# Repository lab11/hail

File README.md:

Hail
====

Hail is an IoT development module that runs the
[Tock](https://github.com/helena-project/tock) operating system.
Its features:

- [SAM4L](http://www.atmel.com/products/microcontrollers/arm/sam4l.aspx) Cortex-M4
- [nRF51822](https://www.nordicsemi.com/eng/Products/Bluetooth-low-energy/nRF51822) BLE Radio
- [SI7021](https://www.silabs.com/products/sensors/humidity-sensors/Pages/si7013-20-21.aspx) Temperature and Humidity Sensor
- [ISL29035](https://www.intersil.com/en/products/optoelectronics/ambient-light-sensors/light-to-digital-sensors/ISL29035.html) Light Sensor
- [FXOS8700CQ](http://www.nxp.com/products/sensors/6-axis-sensors/digital-sensor-3d-accelerometer-2g-4g-8g-plus-3d-magnetometer:FXOS8700CQ) 6-axis Accelerometer and Magnetometer
- RGB LED
- USB Programming
- Particle [Photon](https://www.particle.io/products/hardware/photon-wifi-dev-kit) Form-Factor and Pinout

**[Buy Now!](https://www.tockos.org/hardware/)**

Hail + Tock
-----------

[TockOS](https://github.com/helena-project/tock/tree/master/boards/hail)
supports Hail. See the instructions there for how to program the Tock kernel
and applications.

Bootloader
----------

Hail supports a software bootloader which allows new code to be flashed
over USB. The bootloader source is in the [bootloader](bootloader) directory.
The [tockloader](https://github.com/helena-project/tockloader) utility
can flash applications using the bootloader.

Commissioning New Hail Boards
-----------------------------

There a couple steps to provision a newly populated Hail board.
See the [commissioning](commissioning) folder for more information.

nRF51822 BLE Radio
------------------

By default, the nRF51822 is commissioned with the
[serialization](https://github.com/helena-project/tock-nrf-serialization)
application which allows softdevice commands to be sent over a UART connection
from the SAM4L.

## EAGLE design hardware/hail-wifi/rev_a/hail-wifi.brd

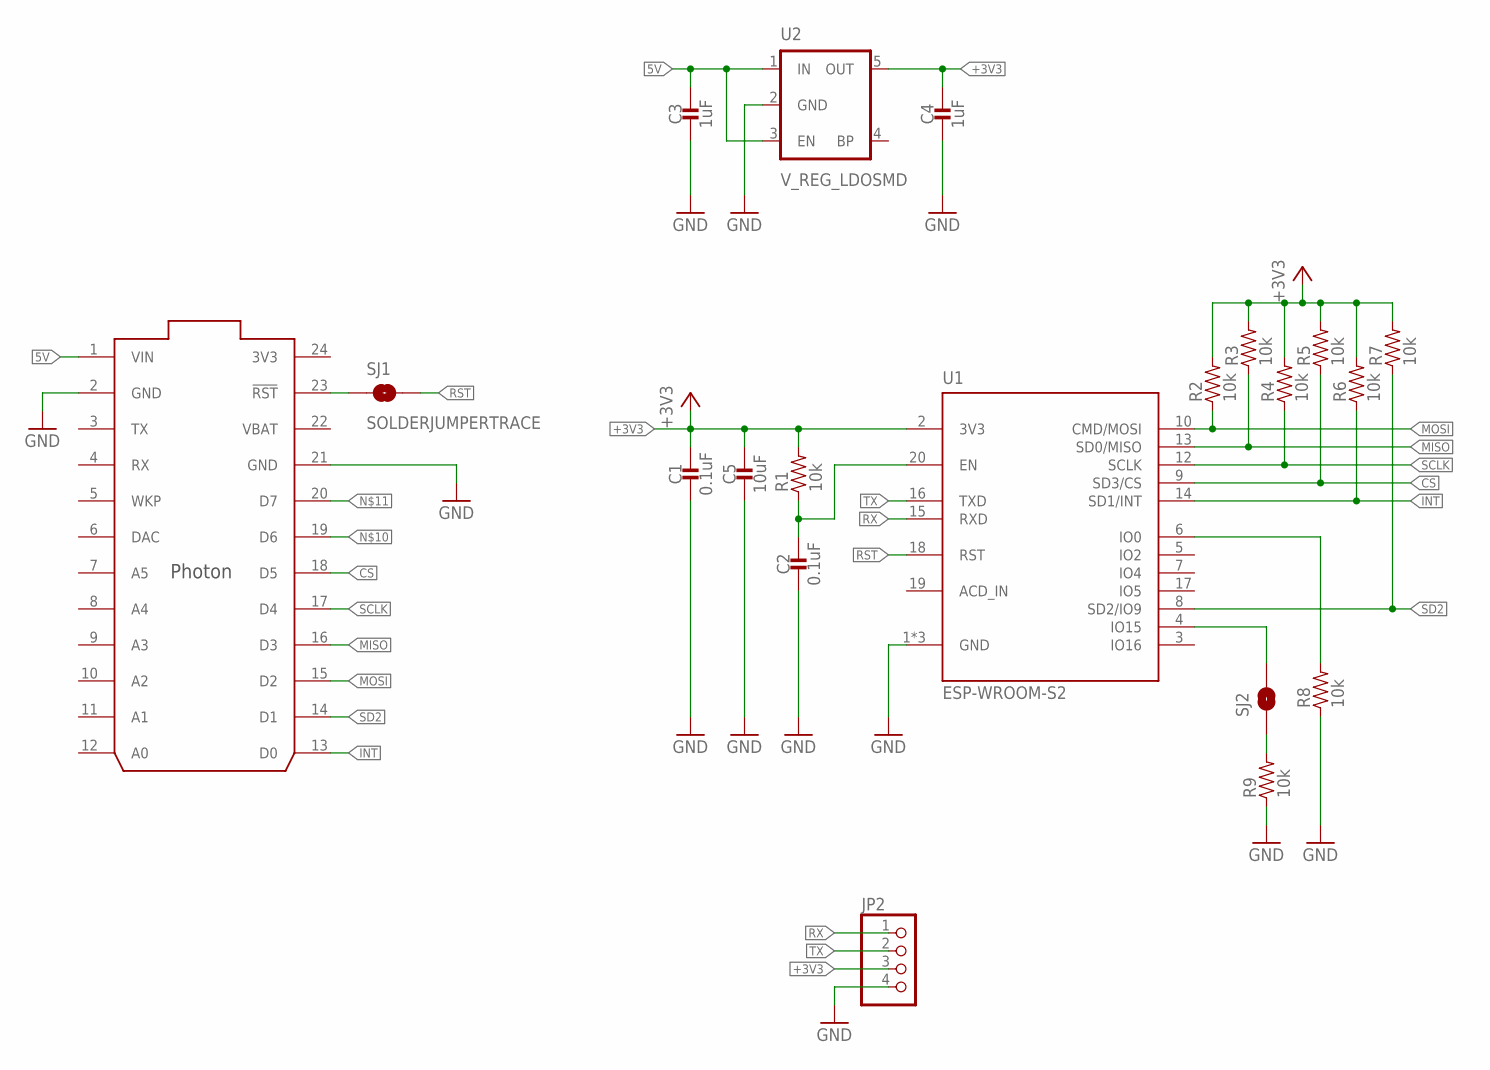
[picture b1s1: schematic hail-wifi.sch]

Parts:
C1, C2: 0.1uF; 0603_CAP
C3, C4: 1uF; 0603_CAP
C5: 10uF; 0603_CAP
JP2: PINHD-1X4/90; 1X04/90
R1, R2, R3, R4, R5, R6, R7, R8, R9: 10k; 0603-RES
SJ1: SOLDERJUMPERTRACE; SJ_2S-TRACE
SJ2: SOLDERJUMPERNO; SJ_2S-NO
U1: ESP-WROOM-S2
U2: V_REG_LDOSMD; SOT23-5
U3: PHOTON_WITH_HEADERS; PHOTON

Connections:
3V3: U3.24 (3V3)
5V: C3.1, U2.1 (IN), U2.3 (EN), U3.1 (VIN)
+3V3: C1.1, C4.1, C5.1, JP2.3, R1.2, R2.2, R3.2, R4.2, R5.2, R6.2, R7.2, U1.2 (3V3), U2.5 (OUT)
CS: R5.1, U1.9 (SD3/CS), U3.18 (D5)
GND: C1.2, C2.2, C3.2, C4.2, C5.2, JP2.4, R8.1, R9.1, U1.1 (GND), U1.11 (GND), U1.21 (GND), U2.2 (GND), U3.2 (GND), U3.21 (GND)
INT: R6.1, U1.14 (SD1/INT), U3.13 (D0)
MISO: R3.1, U1.13 (SD0/MISO), U3.16 (D3)
MOSI: R2.1, U1.10 (CMD/MOSI), U3.15 (D2)
unnamed: SJ2.2, U1.4 (IO15)
unnamed: SJ1.1, U3.23 (!RST)
unnamed: R9.2, SJ2.1
unnamed: R8.2, U1.6 (IO0)
unnamed: C2.1, R1.1, U1.20 (EN)
RST: SJ1.2, U1.18 (RST)
RX: JP2.1, U1.15 (RXD)
SCLK: R4.1, U1.12 (SCLK), U3.17 (D4)
SD2: R7.1, U1.8 (SD2/IO9), U3.14 (D1)
TX: JP2.2, U1.16 (TXD)
VBAT: U3.22 (VBAT)

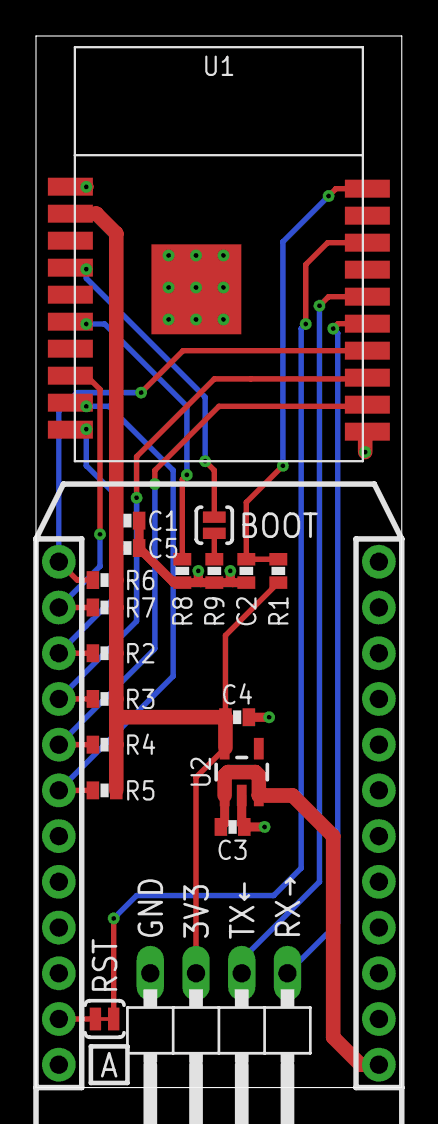
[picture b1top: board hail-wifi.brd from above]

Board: 2 copper layers, 20.3 x 58.4 mm, 20 parts (0 on the bottom side), 17 nets.

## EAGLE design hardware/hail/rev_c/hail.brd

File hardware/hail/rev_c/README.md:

Hardware files
==============

Hail was created in [Eagle](http://www.autodesk.com/products/eagle/overview) and the `hail.sch` and
`hail.brd` files are Eagle schematic and board files respectively.

`hail_bom.xlsx` is the Bill of Materials (list of parts). It is also provided
as `.txt` and `.csv` files for convenience.

Rev C changes
-------------

 * Connected ADVREFP to VDDANA.
 * Replace Lab11 logo with text. In practice, it didn't print correctly.

License
-------

<br />
This work is licensed under a
<a rel="license" href="http://creativecommons.org/licenses/by-sa/4.0/">Creative Commons Attribution-ShareAlike 4.0 International License</a>.

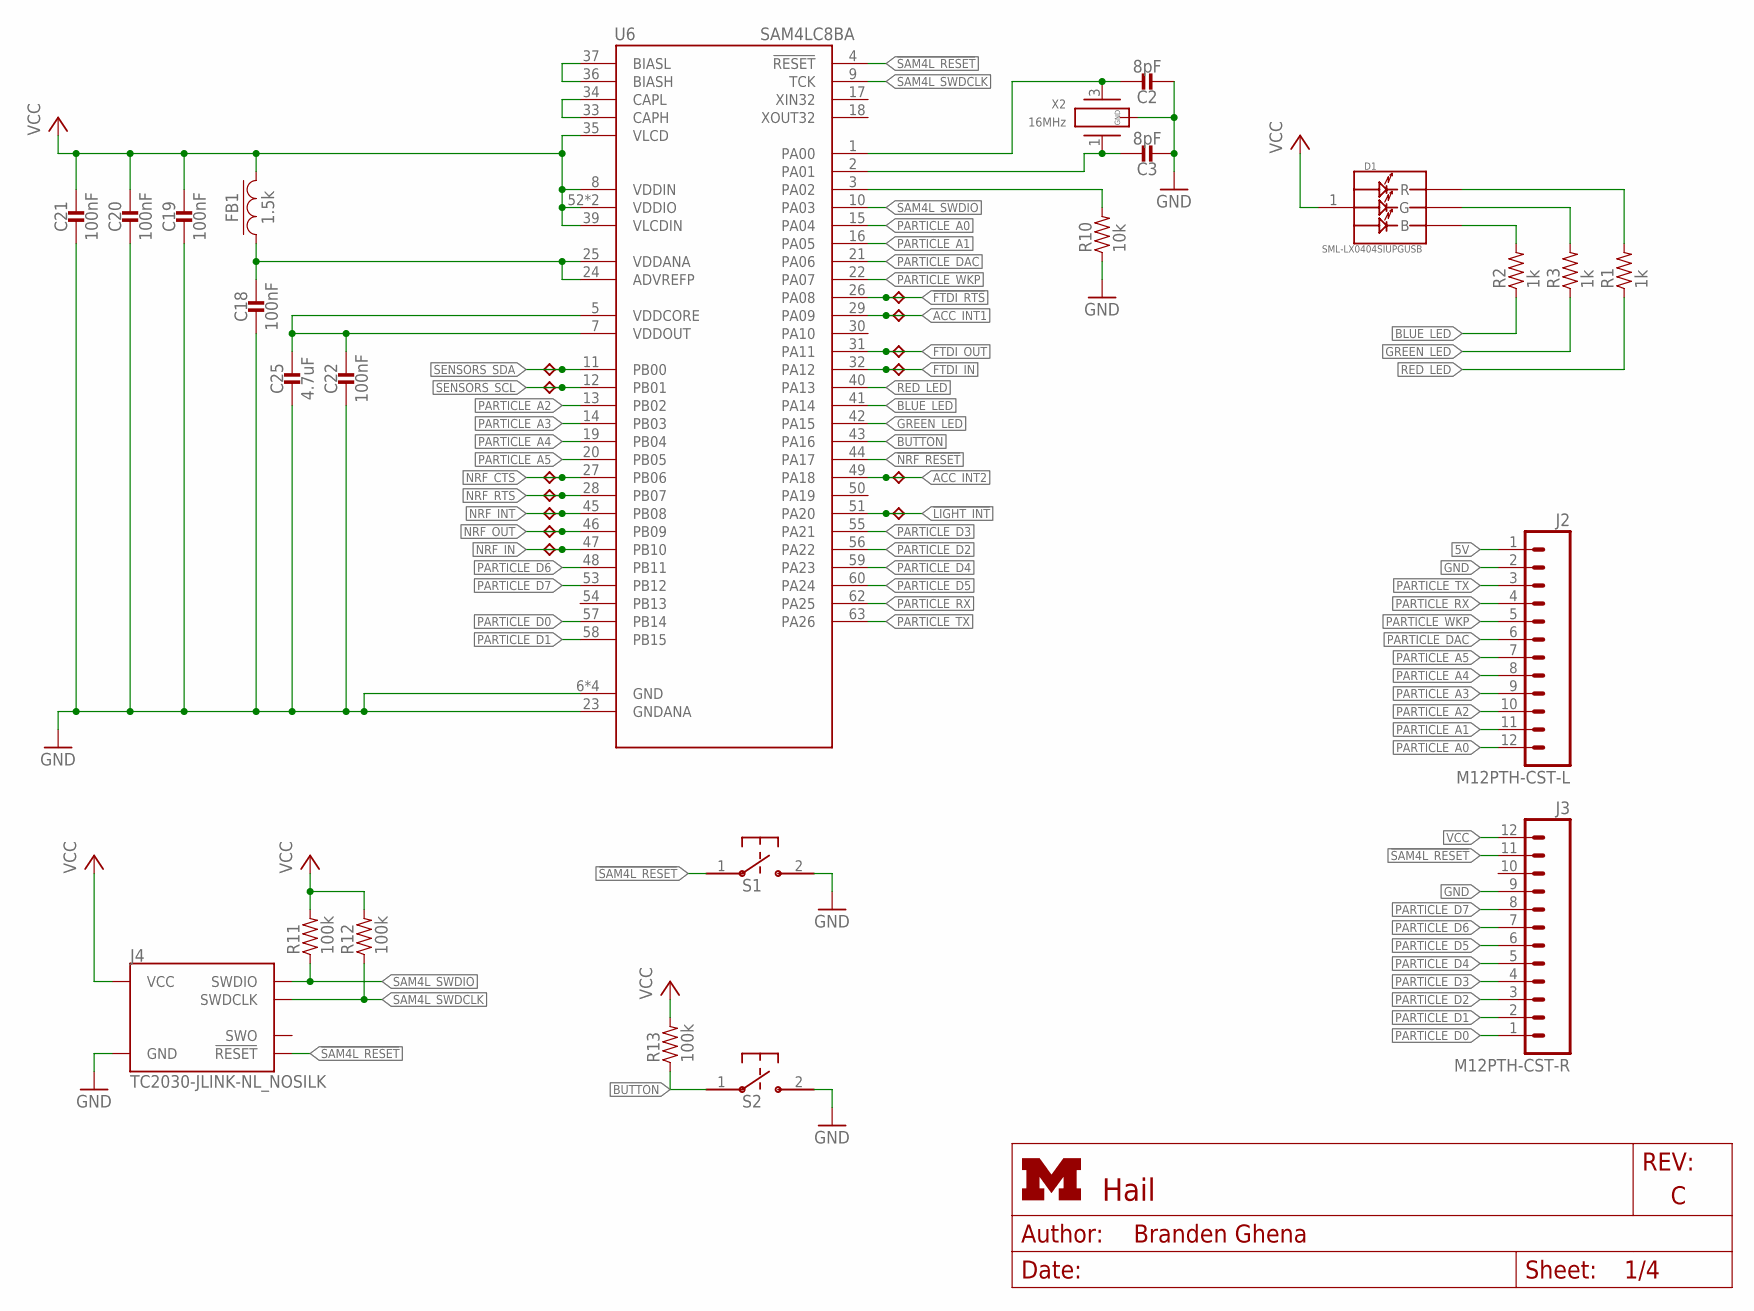
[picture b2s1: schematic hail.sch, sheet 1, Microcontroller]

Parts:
C2, C3: 8pF; 0402_CAP; MPN GRM1555C1H8R0BA01D; DIGIKEY 490-8230-1-ND
C18, C19, C20, C21, C22: 100nF; 0402_CAP; MPN MF-CAP-0402-0.1uF; DIGIKEY 490-10777-1-ND
C25: 4.7uF; 0402_CAP; MPN ZRB15XR61A475KE01D; DIGIKEY 490-13252-1-ND
D1: SML-LX0404SIUPGUSB; 1MM_SQ_4PAD; MPN SML-LX0404SIUPGUSB
FB1: 1.5k; 0402_CAP; MPN CIM05J152NC; DIGIKEY 1276-6395-1-ND
J2: M12PTH-CST-L; 1X12-CASTELLATED; MPN MF-CON-2.54mm-01x12; DIGIKEY S1011E-12-ND
J3: M12PTH-CST-R; 1X12-CASTELLATED; MPN MF-CON-2.54mm-01x12; DIGIKEY S1011E-12-ND
J4: TC2030-JLINK-NL_NOSILK; TC2030-IDC-NL_NOSILK
R1, R2, R3: 1k; 0402_RES; MPN MF-RES-0402-1K; DIGIKEY 1276-3430-1-ND
R10: 10k; 0402_RES; MPN MF-RES-0402-10K; DIGIKEY 1276-3431-1-ND
R11, R12, R13: 100k; 0402_RES; MPN MF-RES-0402-100K; DIGIKEY 1276-3432-1-ND
S1, S2: B3U-1000P; MPN B3U-1000P
TP1, TP2, TP3, TP4, TP5, TP6, TP7, TP8, TP9, TP10, TP11, TP12, TP13: TPB1,27; B1,27
U6: SAM4LC8BA; QFN-64-9MM; MPN ATSAM4LC8BA-MU; DIGIKEY ATSAM4LC8BA-MURCT-ND
X2: 16MHz; FHXXX; MPN FH1600015

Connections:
5V: J2.1 (12); also elsewhere on the board
!FTDI_RTS: TP11.TP, U6.26 (PA08); also elsewhere on the board
!LIGHT_INT: TP10.TP, U6.51 (PA20); also elsewhere on the board
!NRF_RESET: U6.44 (PA17); also elsewhere on the board
!SAM4L_RESET: J3.11, J4.3 (!RESET), S1.1, U6.4 (!RESET); also elsewhere on the board
ACC_INT1: TP8.TP, U6.29 (PA09); also elsewhere on the board
ACC_INT2: TP9.TP, U6.49 (PA18); also elsewhere on the board
BLUE_LED: R2.1, U6.41 (PA14)
BUCK/LDO_N1: R10.2, U6.3 (PA02)
BUTTON: R13.1, S2.1, U6.43 (PA16)
FTDI_IN: TP13.TP, U6.32 (PA12); also elsewhere on the board
FTDI_OUT: TP12.TP, U6.31 (PA11); also elsewhere on the board
GND: C2.2, C3.2, C18.2, C19.2, C20.2, C21.2, C22.2, C25.2, J2.2 (11), J3.9, J4.5 (GND), R10.1, S1.2, S2.2, U6.6 (GND), U6.23 (GNDANA), U6.38 (GND), U6.64 (GND), U6.GND, X2.2 (GND), X2.4 (GND); also elsewhere on the board
GREEN_LED: R3.1, U6.42 (PA15)
unnamed: D1.3 (B), R2.2
unnamed: D1.4 (G), R3.2
unnamed: D1.2 (R), R1.2
unnamed: U6.36 (BIASH), U6.37 (BIASL)
unnamed: U6.33 (CAPH), U6.34 (CAPL)
unnamed: C18.1, FB1.1, U6.24 (ADVREFP), U6.25 (VDDANA)
unnamed: C22.1, C25.1, U6.5 (VDDCORE), U6.7 (VDDOUT)
NRF_CTS: TP1.TP, U6.27 (PB06); also elsewhere on the board
NRF_IN: TP5.TP, U6.47 (PB10); also elsewhere on the board
NRF_INT: TP3.TP, U6.45 (PB08); also elsewhere on the board
NRF_OUT: TP4.TP, U6.46 (PB09); also elsewhere on the board
NRF_RTS: TP2.TP, U6.28 (PB07); also elsewhere on the board
PARTICLE_A0: J2.12 (1), U6.15 (PA04)
PARTICLE_A1: J2.11 (2), U6.16 (PA05)
PARTICLE_A2: J2.10 (3), U6.13 (PB02)
PARTICLE_A3: J2.9 (4), U6.14 (PB03)
PARTICLE_A4: J2.8 (5), U6.19 (PB04)
PARTICLE_A5: J2.7 (6), U6.20 (PB05)
PARTICLE_D0: J3.1, U6.57 (PB14)
PARTICLE_D1: J3.2, U6.58 (PB15)
PARTICLE_D2: J3.3, U6.56 (PA22)
PARTICLE_D3: J3.4, U6.55 (PA21)
PARTICLE_D4: J3.5, U6.59 (PA23)
PARTICLE_D5: J3.6, U6.60 (PA24)
PARTICLE_D6: J3.7, U6.48 (PB11)
PARTICLE_D7: J3.8, U6.53 (PB12)
PARTICLE_DAC: J2.6 (7), U6.21 (PA06)
PARTICLE_RX: J2.4 (9), U6.62 (PA25)
PARTICLE_TX: J2.3 (10), U6.63 (PA26)
PARTICLE_WKP: J2.5 (8), U6.22 (PA07)
RED_LED: R1.1, U6.40 (PA13)
SAM4L_SWDCLK: J4.4 (SWDCLK), R12.1, U6.9 (TCK)
SAM4L_SWDIO: J4.2 (SWDIO), R11.1, U6.10 (PA03)
SAM4L_XIN1: C2.1, U6.1 (PA00), X2.3 (2)
SAM4L_XOUT1: C3.1, U6.2 (PA01), X2.1
SENSORS_SCL: TP7.TP, U6.12 (PB01); also elsewhere on the board
SENSORS_SDA: TP6.TP, U6.11 (PB00); also elsewhere on the board
VCC: C19.1, C20.1, C21.1, D1.1 (VDD), FB1.2, J3.12, J4.1 (VCC), R11.2, R12.2, R13.2, U6.8 (VDDIN), U6.35 (VLCD), U6.39 (VLCDIN), U6.52 (VDDIO), U6.61 (VDDIO); also elsewhere on the board

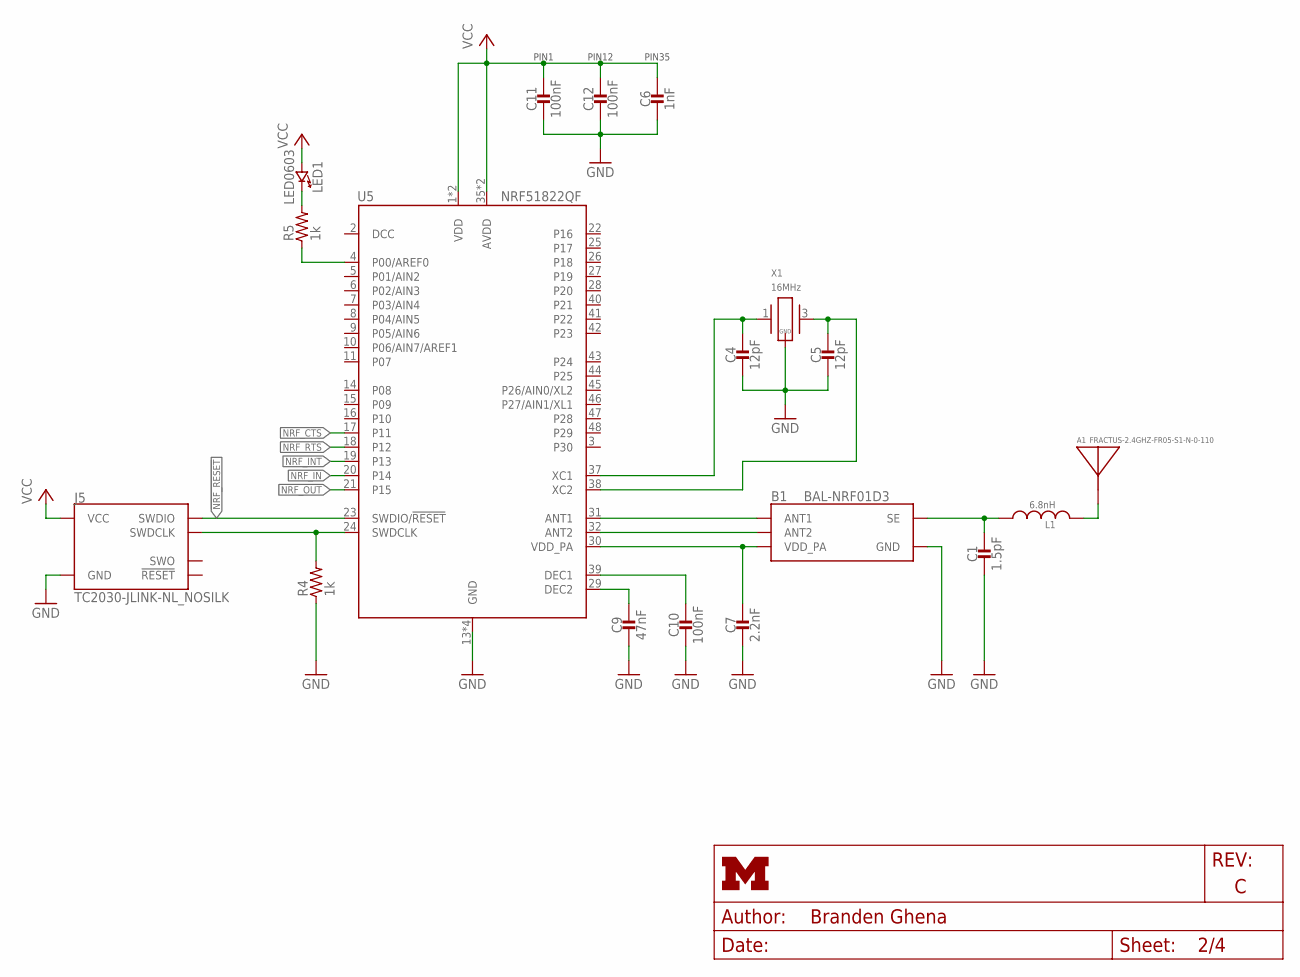
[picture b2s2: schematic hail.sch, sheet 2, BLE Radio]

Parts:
A1: FRACTUS-2.4GHZ-FR05-S1-N-0-110; FRACTUS-ANTENNA-FR05-S1-N-0-110; MPN FR05-S1-N-0110B
B1: BAL-NRF01D3; MPN BAL-NRF01D3
C1: 1.5pF; 0402_CAP; MPN GRM1555C1H1R5BA01D; DIGIKEY 490-6212-1-ND
C4, C5: 12pF; 0402_CAP; MPN GRM1555C1H120GA01D; DIGIKEY 490-6197-1-ND
C6: 1nF; 0402_CAP; MPN MF-CAP-0402-1nF; DIGIKEY 490-1303-1-ND
C7: 2.2nF; 0402_CAP; MPN GRM155R71E222KA01D; DIGIKEY 490-5419-1-ND
C9: 47nF; 0402_CAP; MPN C1005X7R1C473K050BC; DIGIKEY 445-1264-1-ND
C10, C11, C12: 100nF; 0402_CAP; MPN MF-CAP-0402-0.1uF; DIGIKEY 490-10777-1-ND
J5: TC2030-JLINK-NL_NOSILK; TC2030-IDC-NL_NOSILK
L1: 6.8nH; 0402_CAP; MPN LQW15AN6N8G00D; DIGIKEY 490-6840-1-ND
LED1: LED0603; LED-0603; MPN MF-LED-0603-GREEN; DIGIKEY 160-1837-6-ND
R4, R5: 1k; 0402_RES; MPN MF-RES-0402-1K; DIGIKEY 1276-3430-1-ND
U5: NRF51822QF; QFN-48-6MM; MPN NRF51822-QFAC-R7; DIGIKEY 1490-1049-1-ND
X1: 16MHz; TXC-8Y; MPN 8Y-16.000MAAV-T; DIGIKEY 887-2003-1-ND

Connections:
!NRF_RESET: J5.2 (SWDIO), U5.23 (SWDIO/!RESET); also elsewhere on the board
GND: B1.GND, C1.2, C4.2, C5.2, C6.2, C7.2, C9.2, C10.2, C11.2, C12.2, J5.5 (GND), R4.1, U5.13 (GND), U5.33 (GND), U5.34 (GND), U5.GND, X1.2 (GND), X1.4 (GND); also elsewhere on the board
unnamed: C10.1, U5.39 (DEC1)
unnamed: C9.1, U5.29 (DEC2)
unnamed: J5.4 (SWDCLK), R4.2, U5.24 (SWDCLK)
unnamed: R5.1, U5.4 (P00/AREF0)
unnamed: LED1.C (CATHODE), R5.2
unnamed: B1.ANT1, U5.31 (ANT1)
unnamed: B1.VCC (VDD_PA), C7.1, U5.30 (VDD_PA)
unnamed: B1.ANT2, U5.32 (ANT2)
unnamed: C4.1, U5.37 (XC1), X1.1
unnamed: C5.1, U5.38 (XC2), X1.3 (2)
unnamed: B1.SE, C1.1, L1.1
unnamed: A1.ANT, L1.2
NRF_CTS: U5.17 (P11); also elsewhere on the board
NRF_IN: U5.20 (P14); also elsewhere on the board
NRF_INT: U5.19 (P13); also elsewhere on the board
NRF_OUT: U5.21 (P15); also elsewhere on the board
NRF_RTS: U5.18 (P12); also elsewhere on the board
VCC: C6.1, C11.1, C12.1, J5.1 (VCC), LED1.A (ANODE), U5.1 (VDD), U5.12 (VDD), U5.35 (AVDD), U5.36 (AVDD); also elsewhere on the board

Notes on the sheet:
PIN35
PIN1
PIN12

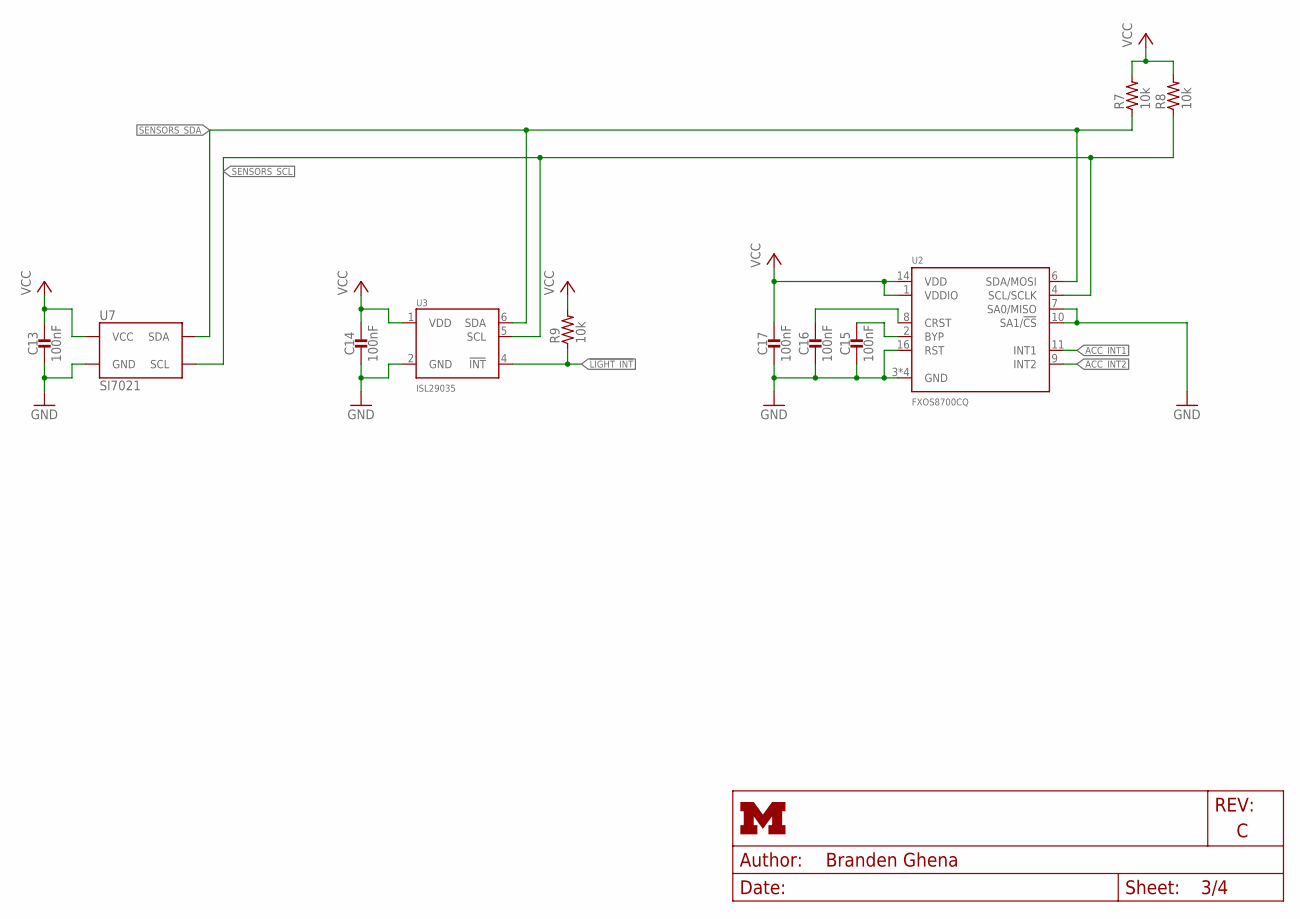
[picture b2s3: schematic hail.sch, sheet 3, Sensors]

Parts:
C13, C14, C15, C16, C17: 100nF; 0402_CAP; MPN MF-CAP-0402-0.1uF; DIGIKEY 490-10777-1-ND
R7, R8, R9: 10k; 0402_RES; MPN MF-RES-0402-10K; DIGIKEY 1276-3431-1-ND
U2: FXOS8700CQ; QFN-16-3MM
U3: ISL29035; ODFN-6-1.5MMX1.6MM
U7: SI7021; DFN-6/3MM; MPN SI7021-A20-GM1; DIGIKEY 336-3141-ND

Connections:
!LIGHT_INT: R9.1, U3.4 (!INT); also elsewhere on the board
ACC_INT1: U2.11 (INT1); also elsewhere on the board
ACC_INT2: U2.9 (INT2); also elsewhere on the board
GND: C13.2, C14.2, C15.2, C16.2, C17.2, U2.3 (GND), U2.5 (GND), U2.7 (SA0/MISO), U2.10 (SA1/!CS), U2.12 (GND), U2.13 (GND), U2.16 (RST), U3.2 (GND), U7.2 (GND); also elsewhere on the board
unnamed: C15.1, U2.2 (BYP)
unnamed: C16.1, U2.8 (CRST)
SENSORS_SCL: R8.1, U2.4 (SCL/SCLK), U3.5 (SCL), U7.6 (SCL); also elsewhere on the board
SENSORS_SDA: R7.1, U2.6 (SDA/MOSI), U3.6 (SDA), U7.1 (SDA); also elsewhere on the board
VCC: C13.1, C14.1, C17.1, R7.2, R8.2, R9.2, U2.1 (VDDIO), U2.14 (VDD), U3.1 (VDD), U7.5 (VCC); also elsewhere on the board

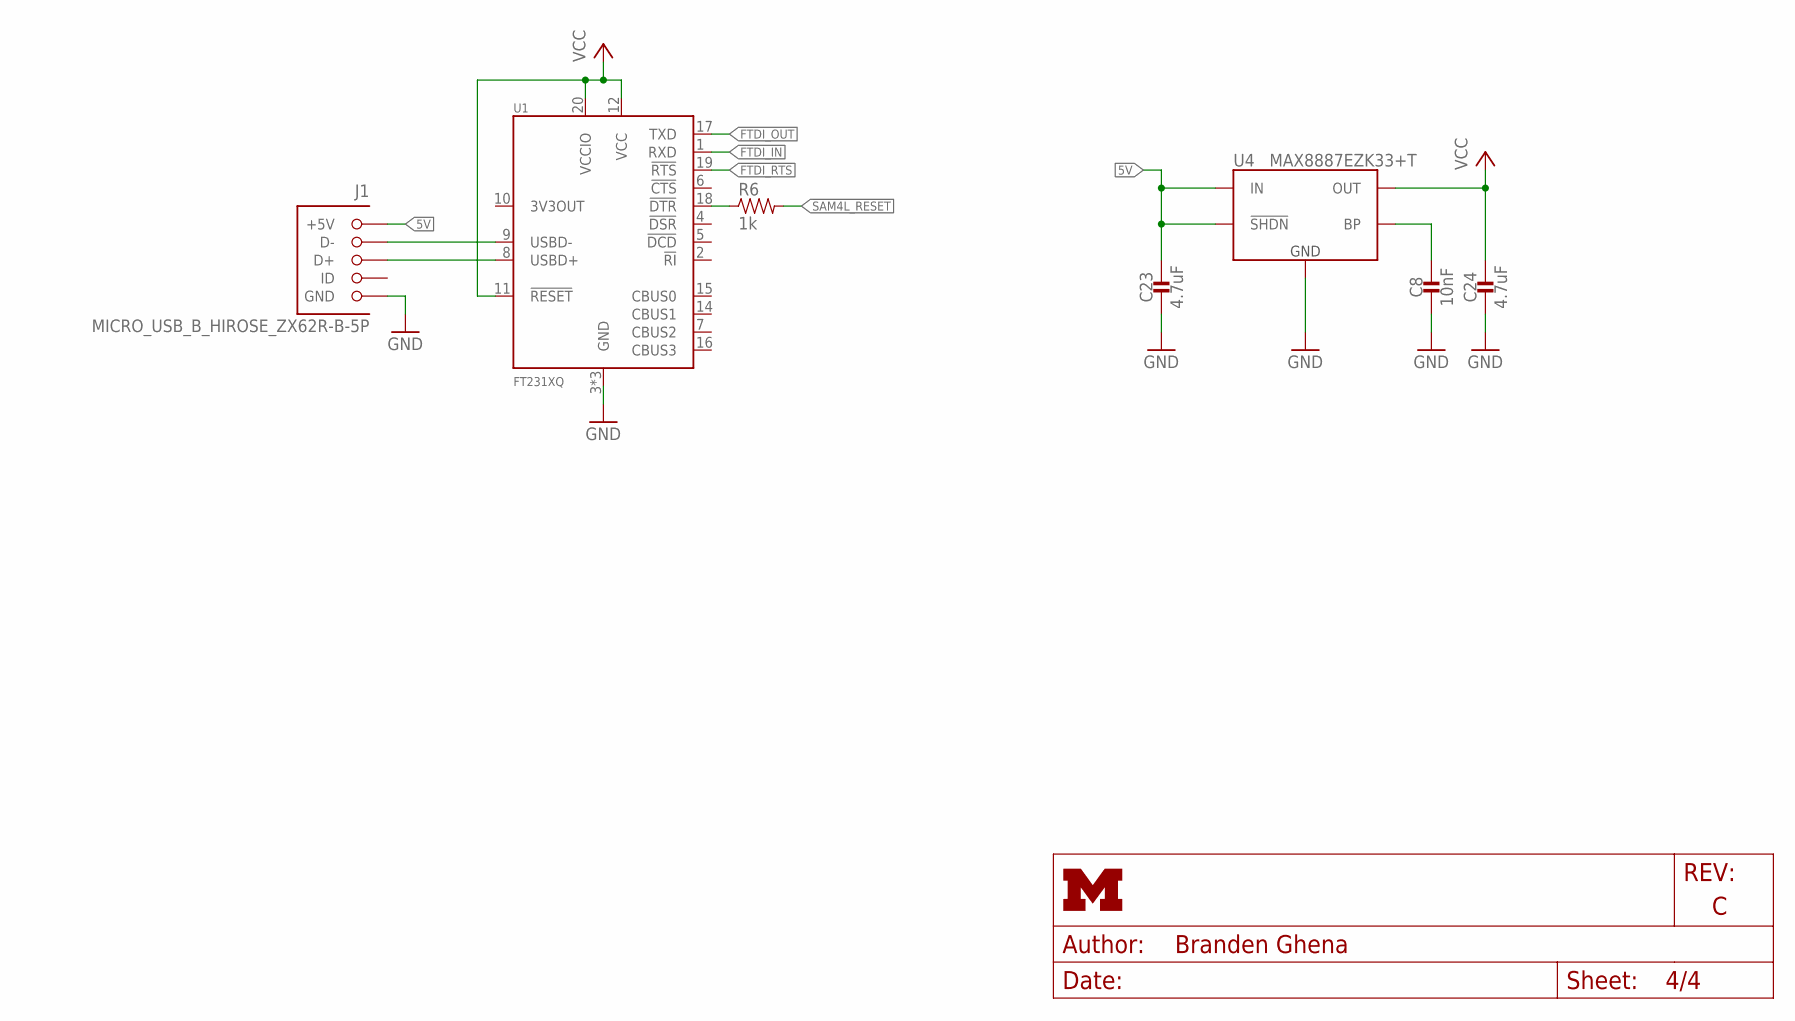
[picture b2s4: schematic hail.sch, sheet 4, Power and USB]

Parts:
C8: 10nF; 0402_CAP; MPN MF-CAP-0402-0.01uF; DIGIKEY 490-7763-1-ND
C23, C24: 4.7uF; 0402_CAP; MPN ZRB15XR61A475KE01D; DIGIKEY 490-13252-1-ND
J1: MICRO_USB_B_HIROSE_ZX62R-B-5P; USB_MICRO_B-HIROSE-ZX62R-B-5P; MPN ZX62R-B-5P(30); DIGIKEY H125274CT-ND
R6: 1k; 0402_RES; MPN MF-RES-0402-1K; DIGIKEY 1276-3430-1-ND
U1: FT231XQ; QFN-20-4MM
U4: MAX8887EZK33+T; SOT-23-5; MPN MAX8887EZK33+T

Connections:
5V: C23.1, J1.1 (+5V), U4.1 (IN), U4.3 (!SHDN); also elsewhere on the board
!FTDI_RTS: U1.19 (!RTS); also elsewhere on the board
!SAM4L_RESET: R6.2; also elsewhere on the board
FTDI_IN: U1.1 (RXD); also elsewhere on the board
FTDI_OUT: U1.17 (TXD); also elsewhere on the board
GND: C8.2, C23.2, C24.2, J1.5 (GND), U1.3 (GND), U1.13 (GND), U1.GND, U4.2 (GND); also elsewhere on the board
unnamed: J1.2 (D-), U1.9 (USBD-)
unnamed: J1.3 (D+), U1.8 (USBD+)
unnamed: C8.1, U4.4 (BP)
unnamed: R6.1, U1.18 (!DTR)
VCC: C24.1, U1.11 (!RESET), U1.12 (VCC), U1.20 (VCCIO), U4.5 (OUT); also elsewhere on the board

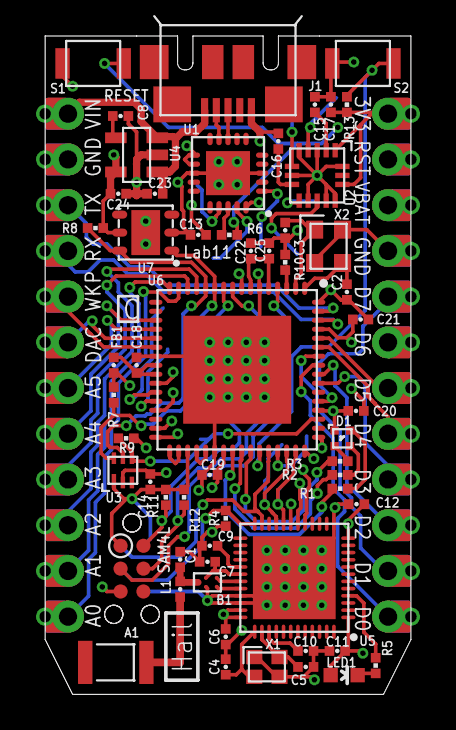
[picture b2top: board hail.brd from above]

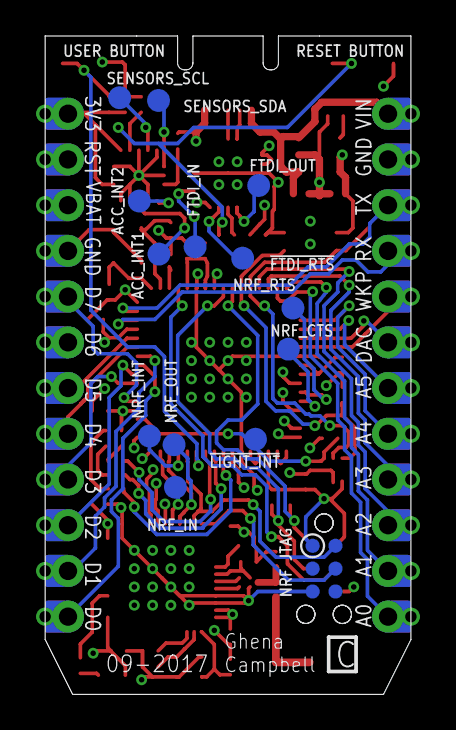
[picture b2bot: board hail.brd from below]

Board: 4 copper layers, 20.3 x 36.6 mm, 75 parts (14 on the bottom side), 70 nets.

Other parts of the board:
U$1: PHOTON-BOTTOM-SS
U$2: PHOTON-TOP-SS

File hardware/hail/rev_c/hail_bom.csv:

# Bill of Materials,,,,,,,,,
# Converted from {},,,,,,,,,
# Generated by bom_to_text.py,,,,,,,,,
#,,,,,,,,,
,,,,,,,,,
Qty,Value,Device,Package,Parts,Description,MPN,DIGIKEY,MOUSER,RICHARDSON_RFPD
1,FRACTUS-2.4GHZ-FR05-S1-N-0-110,FRACTUS-2.4GHZ-FR05-S1-N-0-110,FRACTUS-ANTENNA-FR05-S1-N-0-110,A1,Fractus Micro Reach Xtend,,,,FR05-S1-N-0110B
1,BAL-NRF01D3,BAL-NRF01D3,BAL-NRF01D3,B1,"50 ohm nominal input / conjugate match balun to nRF51422-QFAA,",,497-13637-1-ND,511-BAL-NRF01D3,
1,1.5pF,CAPACITOR0402_CAP,0402_CAP,C1,0402 Capacitor,,490-6212-1-ND,,
2,8pF,CAPACITOR0402_CAP,0402_CAP,"C2, C3",0402 Capacitor,,490-8230-1-ND,,
2,12pF,CAPACITOR0402_CAP,0402_CAP,"C4, C5",0402 Capacitor,,490-6197-1-ND,,
1,1nF,CAPACITOR0402_CAP,0402_CAP,C6,0402 Capacitor,,490-1303-1-ND,,
1,2.2nF,CAPACITOR0402_CAP,0402_CAP,C7,0402 Capacitor,,490-5419-1-ND,,
1,10nF,CAPACITOR0402_CAP,0402_CAP,C8,0402 Capacitor,,490-7763-1-ND,,
1,47nF,CAPACITOR0402_CAP,0402_CAP,C9,0402 Capacitor,,445-1264-1-ND,,
13,100nF,CAPACITOR0402_CAP,0402_CAP,"C10, C11, C12, C13, C14, C15, C16, C17, C18, C19, C20, C21, C22",0402 Capacitor,,490-10777-1-ND,,
3,4.7uF,CAPACITOR0402_CAP,0402_CAP,"C23, C24, C25",0402 Capacitor,,490-13252-1-ND,,
1,SML-LX0404SIUPGUSB,SML-LX0404SIUPGUSB,1MM_SQ_4PAD,D1,1mm^2 RGB LED,,67-2125-1-ND,,
1,1.5k,FERRITE_BEAD0402,0402_CAP,FB1,,,1276-6395-1-ND,,
1,MICRO_USB_B_HIROSE_ZX62R-B-5P,MICRO_USB_B_HIROSE_ZX62R-B-5P,USB_MICRO_B-HIROSE-ZX62R-B-5P,J1,USB Micro B Connector,,H125274CT-ND,,
1,M12PTH-CST-L,M12PTH-CST-L,1X12-CASTELLATED,J2,Header 12,,S1011E-12-ND,,
1,M12PTH-CST-R,M12PTH-CST-R,1X12-CASTELLATED,J3,Header 12,,S1011E-12-ND,,
1,6.8nH,INDUCTOR0402,0402_CAP,L1,A very specific inductor,,490-6840-1-ND,,
1,LED0603,LED0603,LED-0603,LED1,LED,,160-1837-6-ND,,
6,1k,RESISTOR0402_RES,0402_RES,"R1, R2, R3, R4, R5, R6",Resistor,,1276-3430-1-ND,,
4,10k,RESISTOR0402_RES,0402_RES,"R7, R8, R9, R10",Resistor,,1276-3431-1-ND,,
3,100k,RESISTOR0402_RES,0402_RES,"R11, R12, R13",Resistor,,1276-3432-1-ND,,
2,B3U-1000P,B3U-1000P,B3U-1000P,"S1, S2",Switch,,SW1020CT-ND,,
1,FT231XQ,FT231XQ,QFN-20-4MM,U1,"USB Bridge, USB to UART USB 2.0 UART Interface",FT231XQ-R,768-1128-1-ND,,
1,FXOS8700CQ,FXOS8700CQ,QFN-16-3MM,U2,"Accelerometer, Magnetometer, 3 Axis Sensor, I2C/SPI",FXOS8700CQR1,FXOS8700CQR1CT-ND,,
1,ISL29035,ISL29035,ODFN-6-1.5MMX1.6MM,U3,Optical Sensor Ambient 550nm I2C,ISL29035IROZ-T7,ISL29035IROZ-T7CT-ND,,
1,MAX8887EZK33+T,MAX8887EZK33+T,SOT-23-5,U4,IC REG LDO 3.3V 0.3A TSOT23-5,,MAX8887EZK33+TCT-ND,,
1,NRF51822QF,NRF51822QF,QFN-48-6MM,U5,Multiprotocol Bluetooth 4.0 low energy/2.4 GHz RF SoC,,1490-1049-1-ND,,
1,SAM4LC8BA,SAM4LC8BA,QFN-64-9MM,U6,SAM4L Microcontroller. 64QFN Package. 512 Flash.,,ATSAM4LC8BA-MURCT-ND,,
1,SI7021,SI7021,DFN-6/3MM,U7,IC TEMP SENSOR RH 2% DFN,,336-3141-ND,,
1,16MHz,TXC-8Y,TXC-8Y,X1,2mmx1.6mm SMD Crystal,,887-2003-1-ND,,
1,16MHz,FH1600015,FHXXX,X2,Pericom Type FH 16 MHz 2.5 x 2.0 mm,,FH1600015CT-ND,,

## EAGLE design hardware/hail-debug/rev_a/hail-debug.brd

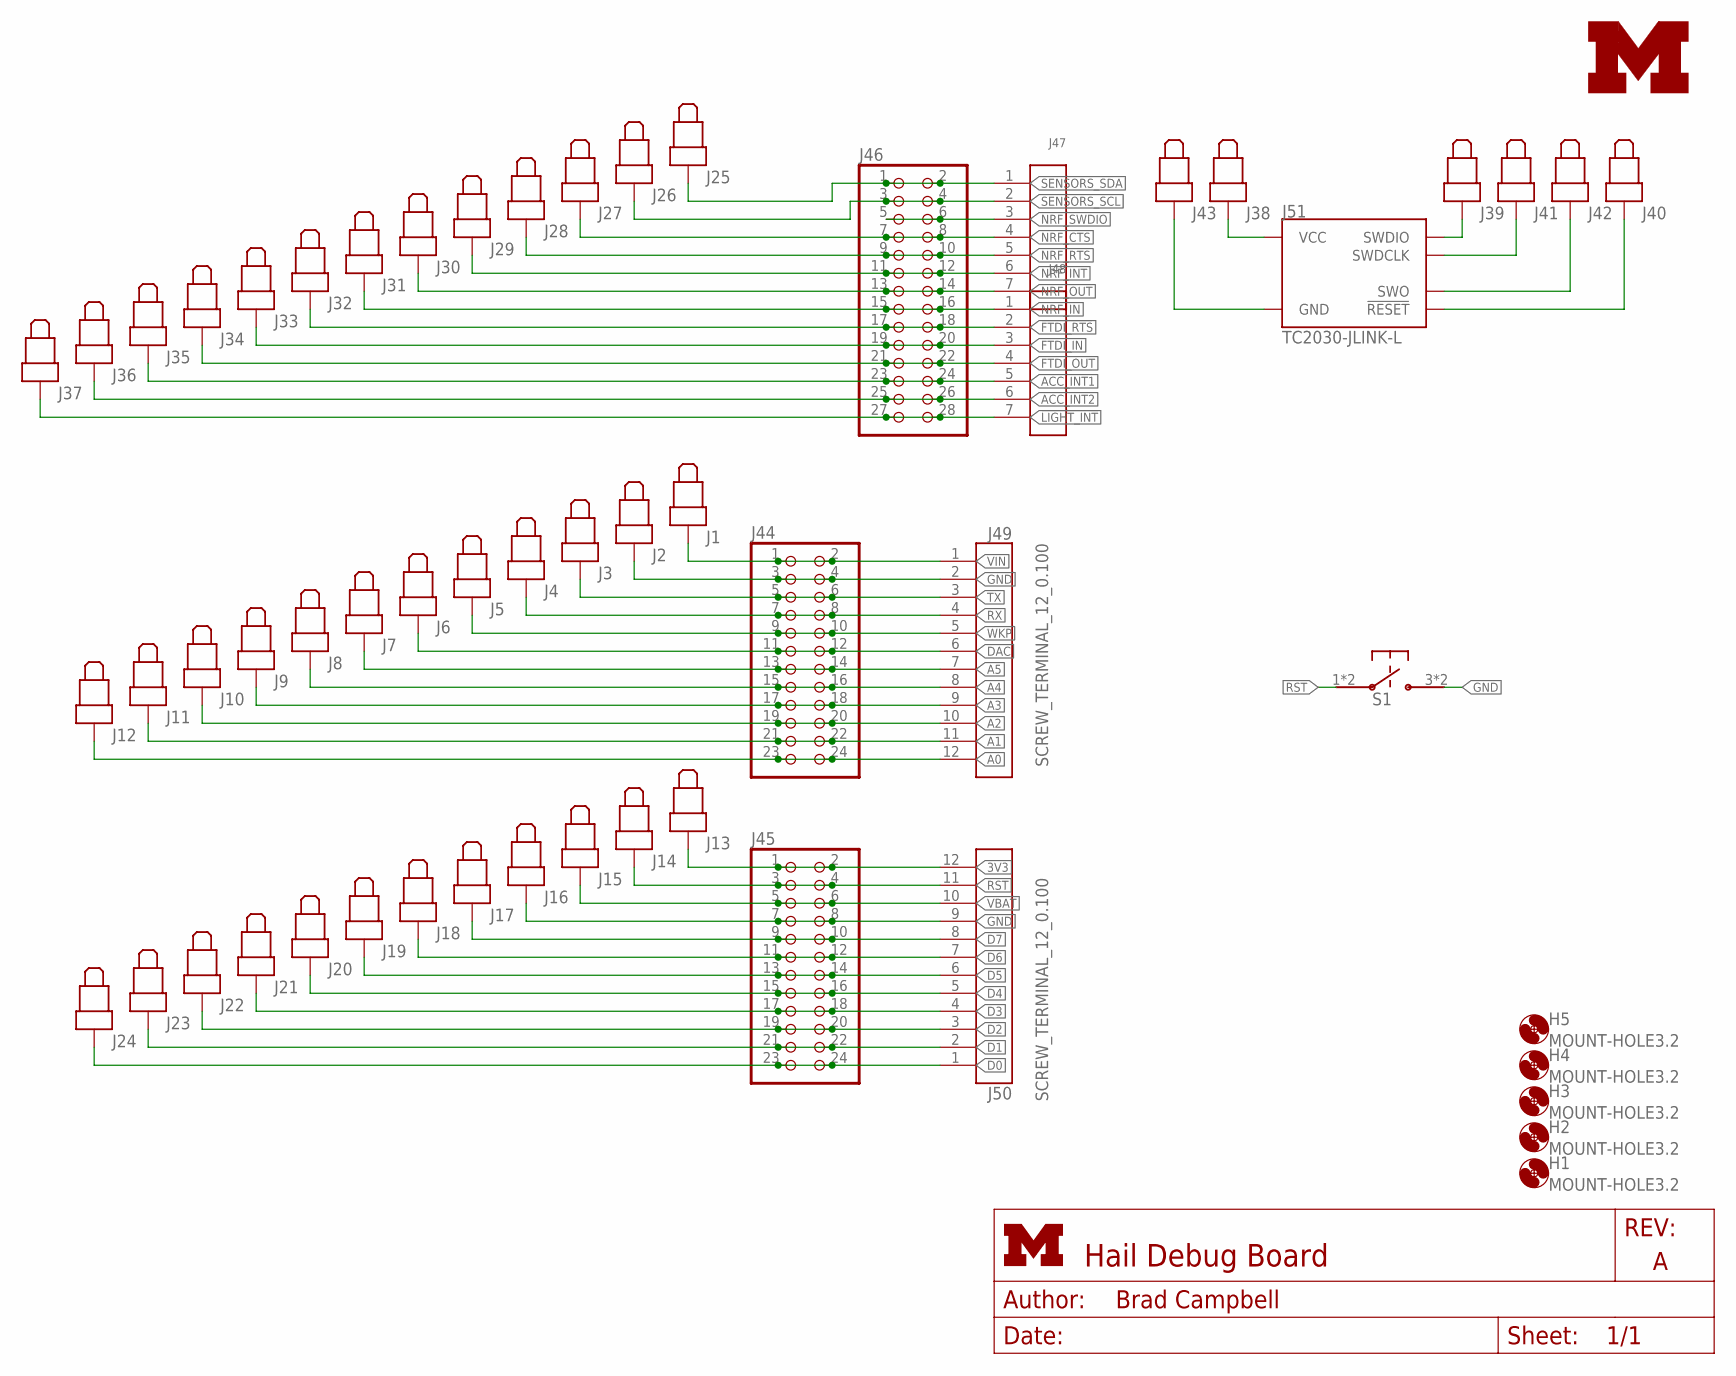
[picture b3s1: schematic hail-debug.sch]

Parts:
H1, H2, H3, H4, H5: MOUNT-HOLE3.2; 3,2
J1, J2, J3, J4, J5, J6, J7, J8, J9, J10, J11, J12, J13, J14, J15, J16, J17, J18, J19, J20, J21, J22, J23, J24: MILLMAX_0908-X-15-20-75-14-11-0; POGO_0908-X-15-20-75-14-11-0
J25, J26, J27, J28, J29, J30, J31, J32, J33, J34, J35, J36, J37, J38, J39, J40, J41, J42, J43: MILLMAX_0985-X-15-20-71-14-11-0; POGO_0985-X-15-20-71-14-11-0
J44, J45: PINHD-2X12; 2X12; DIGIKEY S2011EC-12-ND
J46: PINHD-2X14; 2X14; DIGIKEY S2011EC-14-ND
J47, J48: SCREW-TERMINAL_7_0.100; CONN_BLOCK_7
J49, J50: SCREW_TERMINAL_12_0.100; CONN_BLOCK_12
J51: TC2030-JLINK-L; TC2030-IDC
LOGO1: UMICH_SOLID_SMALL+; UMICH_SOLID_100MIL
S1: PTS645SM43SMTR92; PTS645

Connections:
3V3: J13.P$1, J45.1, J45.2, J50.12
!FTDI_RTS: J32.P1, J46.17, J46.18, J48.2
!LIGHT_INT: J37.P1, J46.27, J46.28, J48.7
!NRF_RESET: J40.P1, J51.3 (!RESET)
A0: J12.P$1, J44.23, J44.24, J49.12
A1: J11.P$1, J44.21, J44.22, J49.11
A2: J10.P$1, J44.19, J44.20, J49.10
A3: J9.P$1, J44.17, J44.18, J49.9
A4: J8.P$1, J44.15, J44.16, J49.8
A5: J7.P$1, J44.13, J44.14, J49.7
ACC_INT1: J35.P1, J46.23, J46.24, J48.5
ACC_INT2: J36.P1, J46.25, J46.26, J48.6
D0: J24.P$1, J45.23, J45.24, J50.1
D1: J23.P$1, J45.21, J45.22, J50.2
D2: J22.P$1, J45.19, J45.20, J50.3
D3: J21.P$1, J45.17, J45.18, J50.4
D4: J20.P$1, J45.15, J45.16, J50.5
D5: J19.P$1, J45.13, J45.14, J50.6
D6: J18.P$1, J45.11, J45.12, J50.7
D7: J17.P$1, J45.9, J45.10, J50.8
DAC: J6.P$1, J44.11, J44.12, J49.6
FTDI_IN: J33.P1, J46.19, J46.20, J48.3
FTDI_OUT: J34.P1, J46.21, J46.22, J48.4
GND: J2.P$1, J16.P$1, J43.P1, J44.3, J44.4, J45.7, J45.8, J49.2, J50.9, J51.5 (GND), S1.3, S1.4
NRF_CTS: J27.P1, J46.7, J46.8, J47.4
NRF_IN: J31.P1, J46.15, J46.16, J48.1
NRF_INT: J29.P1, J46.11, J46.12, J47.6
NRF_OUT: J30.P1, J46.13, J46.14, J47.7
NRF_RTS: J28.P1, J46.9, J46.10, J47.5
NRF_SWDCLK: J41.P1, J51.4 (SWDCLK)
NRF_SWDIO: J39.P1, J46.5, J46.6, J47.3, J51.2 (SWDIO)
NRF_SWO: J42.P1
NRV_VCC: J38.P1, J51.1 (VCC)
RST: J14.P$1, J45.3, J45.4, J50.11, S1.1, S1.2
RX: J4.P$1, J44.7, J44.8, J49.4
SENSORS_SCL: J26.P1, J46.3, J46.4, J47.2
SENSORS_SDA: J25.P1, J46.1, J46.2, J47.1
TX: J3.P$1, J44.5, J44.6, J49.3
VBAT: J15.P$1, J45.5, J45.6, J50.10
VIN: J1.P$1, J44.1, J44.2, J49.1
WKP: J5.P$1, J44.9, J44.10, J49.5

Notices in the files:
parts and their libraries:
Particle-Devices: Licensing: Designed by Particle.
SparkFun-PowerIC: Licensing: CC v3.0 Share-Alike You are welcome to use this library for commercial purposes.
